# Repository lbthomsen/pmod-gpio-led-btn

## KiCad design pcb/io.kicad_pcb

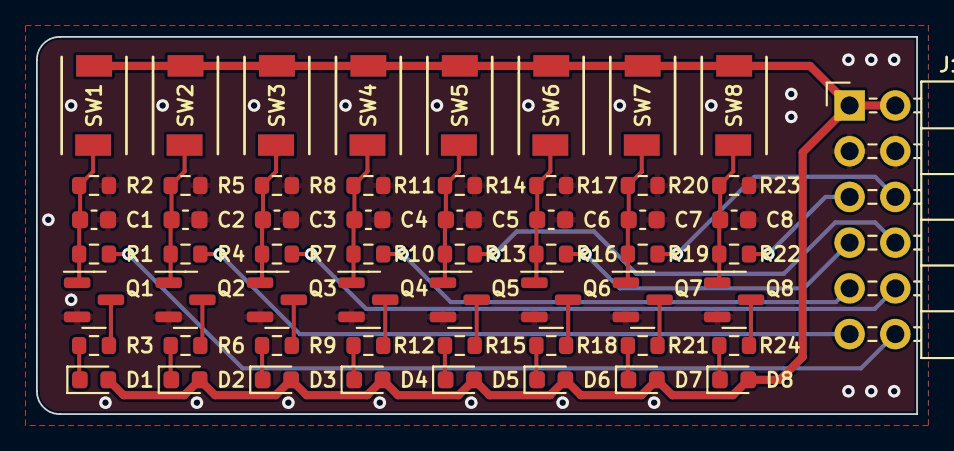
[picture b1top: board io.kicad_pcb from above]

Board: 2 copper layers, 48.9 x 21.0 mm, 57 parts (0 on the bottom side), 34 nets.

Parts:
C1, C2, C3, C4, C5, C6, C7, C8: 100nF; C_0603_1608Metric
D1, D2, D3, D4, D5, D6, D7, D8: LED; LED_0603_1608Metric
J1: PinHeader_2x06_P2.54mm_Horizontal
Q1, Q2, Q3, Q4, Q5, Q6, Q7, Q8: AO3400A; SOT-23
R1, R4, R7, R10, R13, R16, R19, R22: 220; R_0603_1608Metric
R2, R5, R8, R11, R14, R17, R20, R23: 10k; R_0603_1608Metric
R3, R6, R9, R12, R15, R18, R21, R24: 440; R_0603_1608Metric
SW1, SW2, SW3, SW4, SW5, SW6, SW7, SW8: TS-1088R-02526

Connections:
+3.3V: D1.2 (A), D2.2 (A), D3.2 (A), D4.2 (A), D5.2 (A), D6.2 (A), D7.2 (A), D8.2 (A), J1.1, J1.2, SW1.2, SW2.2, SW3.2, SW4.2, SW5.2, SW6.2, SW7.2, SW8.2
GND: C1.2, C2.2, C3.2, C4.2, C5.2, C6.2, C7.2, C8.2, J1.3, J1.4, Q1.2 (S), Q2.2 (S), Q3.2 (S), Q4.2 (S), Q5.2 (S), Q6.2 (S), Q7.2 (S), Q8.2 (S), R2.2, R5.2, R8.2, R11.2, R14.2, R17.2, R20.2, R23.2
L0_0: J1.12, R1.2
L0_1: J1.11, R4.2
L0_2: J1.10, R7.2
L0_3: J1.9, R10.2
L0_4: J1.8, R13.2
L0_5: J1.7, R16.2
L0_6: J1.6, R19.2
L0_7: J1.5, R22.2
unnamed: D1.1 (K), R3.1
unnamed: D2.1 (K), R6.1
unnamed: D3.1 (K), R9.1
unnamed: D4.1 (K), R12.1
unnamed: D5.1 (K), R15.1
unnamed: D6.1 (K), R18.1
unnamed: D7.1 (K), R21.1
unnamed: D8.1 (K), R24.1
unnamed: C1.1, Q1.1 (G), R1.1, R2.1, SW1.1
unnamed: Q1.3 (D), R3.2
unnamed: C2.1, Q2.1 (G), R4.1, R5.1, SW2.1
unnamed: Q2.3 (D), R6.2
unnamed: C3.1, Q3.1 (G), R7.1, R8.1, SW3.1
unnamed: Q3.3 (D), R9.2
unnamed: C4.1, Q4.1 (G), R10.1, R11.1, SW4.1
unnamed: Q4.3 (D), R12.2
unnamed: C5.1, Q5.1 (G), R13.1, R14.1, SW5.1
unnamed: Q5.3 (D), R15.2
unnamed: C6.1, Q6.1 (G), R16.1, R17.1, SW6.1
unnamed: Q6.3 (D), R18.2
unnamed: C7.1, Q7.1 (G), R19.1, R20.1, SW7.1
unnamed: Q7.3 (D), R21.2
unnamed: C8.1, Q8.1 (G), R22.1, R23.1, SW8.1
unnamed: Q8.3 (D), R24.2

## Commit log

2022-11-16 Hmmm
2022-11-16 Hmmmm
2022-11-16 Ready to order
2022-11-25 Bumped revision
2022-12-21 Tweaking

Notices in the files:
pcb/io.kicad_pcb:
(C) 2022 ${AUTHOR}
